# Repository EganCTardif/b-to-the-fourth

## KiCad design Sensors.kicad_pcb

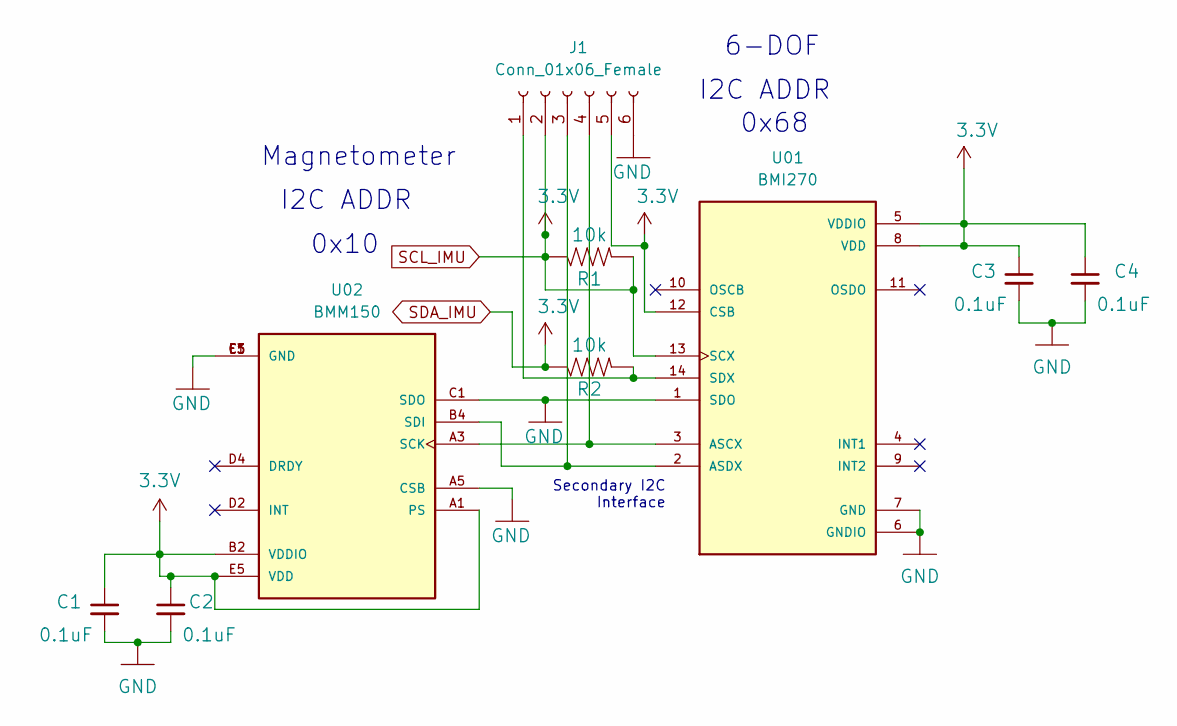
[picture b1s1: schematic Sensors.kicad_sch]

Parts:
C1, C2, C3, C4: 0.1uF; C_0603_1608Metric
J1: Conn_01x06_Female; PinHeader_1x06_P2.54mm_Horizontal
R1, R2: 10k; R_0603_1608Metric
U01: BMI270; XDCR_BMI270
U02: BMM150; XDCR_BMM150

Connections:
GND: C1.2, C2.2, C3.2, C4.2, J1.6, U01.1 (SDO), U01.6 (GNDIO), U01.7 (GND), U02.A5 (CSB), U02.C1 (SDO), U02.C5 (GND), U02.E1 (GND), U02.E3 (GND)
unnamed: J1.1, R2.2, U01.14 (SDX)
unnamed: J1.3, U01.2 (ASDX), U02.B4 (SDI)
unnamed: J1.4, U01.3 (ASCX), U02.A3 (SCK)
SCL_IMU: C1.1, C2.1, C3.1, C4.1, J1.2, J1.5, R1.1, R1.2, R2.1, U01.5 (VDDIO), U01.8 (VDD), U01.12 (CSB), U01.13 (SCX), U02.A1 (PS), U02.B2 (VDDIO), U02.E5 (VDD)

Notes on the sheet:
0x10
Secondary I2C Interface
I2C ADDR
0x68
Magnetometer
6-DOF

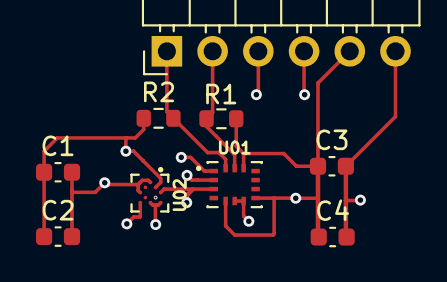
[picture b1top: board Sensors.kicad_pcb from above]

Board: 4 copper layers, 9 parts (0 on the bottom side), 5 nets.

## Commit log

2023-01-15 Added Pin Headers to Schematic and PCB
    6 pin connector for
    sda
    scl
    gnd
    3.3v
    sdi
